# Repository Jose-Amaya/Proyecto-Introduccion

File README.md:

# Proyecto Introducción a la Ingeniería: Información sobre centrales de generación en Colombia

El proyecto consiste, en una estructura con un mapa de Colombia, el cuál tiene en cada punto donde hay una de las 47 centrales escogidas, un LED, el cuál estará encendido si la central en ese punto se encuentra en funcionamiento, y apagado si la central no está en funcionamiento, el color del LED depende del tipo de generación que se da en la central, y además hay un panel en donde se muestra la información de generación para cada central.

# Partes del proyecto

Para el desarrollo del proyecto:
1. Se editó el mapa para agregar la ubicacion de cada central, y las convenciones. [Abrir Carpeta](1.%20Diseño%20mapa/)
2. Se creó un programa en python que corre en una [Raspberri pi 3](https://www.raspberrypi.org/products/raspberry-pi-3-model-b/). [Abrir Carpeta](2.%20Programación/)
3. Se diseño una PCB, para controlar los 47 LEDs, con solo 16 pines ( o menos ) de la raspberry pi ( Por medio de una matriz de LEDS ) [Abrir Carpeta](3.%20PCB/)
4. Se diseño una página web para mostrar los datos de generación de las centrales en un panel. [Abrir Carpeta](4.%20Página%20web/)
5. Se diseño una estructura para contener todos los elementos.
6. Se consiguio información sobre las centrales de xm.com.co [Abrir Archivo Centrales.xlsx](6.%20Archivos/Centrales.xlsx)

Visitar cada carpeta para obtener mas información

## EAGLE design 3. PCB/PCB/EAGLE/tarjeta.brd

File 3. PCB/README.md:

# Archivos

## Orden de conexion

### tarjetaCentrales

En el archivo se encuentra el diseño de la PCB, y en cada puerto se indica la central a la que corresponde

## PCB

### tarjetaPCB

El diseño de la PCB

### tarjetaSchematic

El esquema del circuito

## EAGLE

Archivos del diseño y esquema para el programa [EAGLE](https://www.autodesk.com/education/free-software/eagle) de Autodesk

## Raspberry Pi

### pi3gpio

Numeración de los pines GPIO de la Raspberry Pi 3

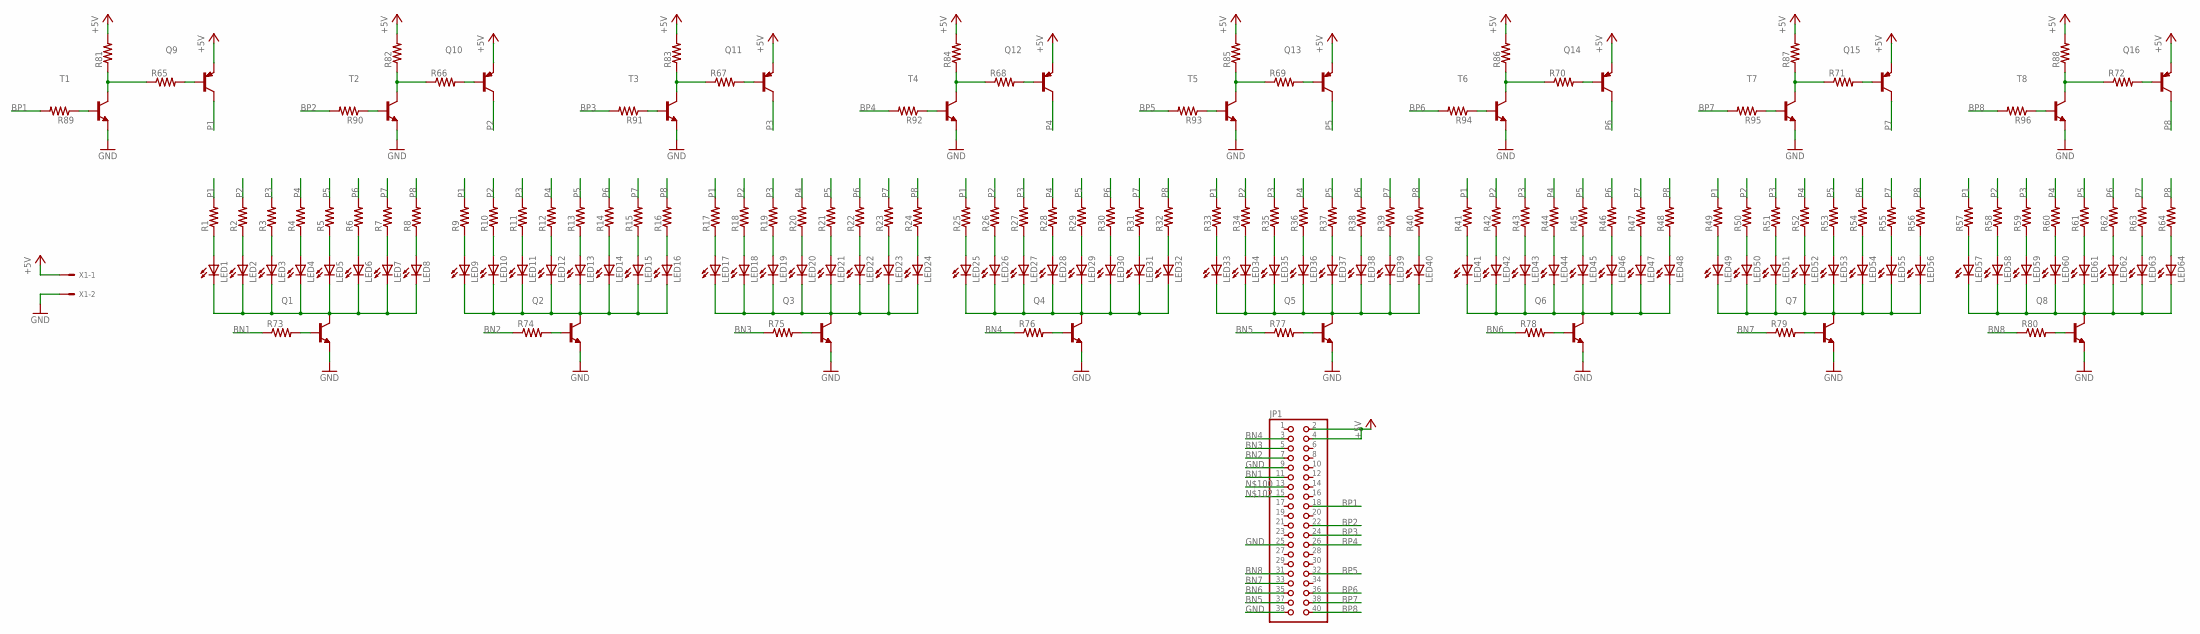
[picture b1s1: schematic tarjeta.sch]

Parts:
JP1: PINHD-2X20; 2X20
LED1, LED2, LED3, LED4, LED5, LED6, LED7, LED8, LED9, LED10, LED11, LED12, LED13, LED14, LED15, LED16, LED17, LED18, LED19, LED20, LED21, LED22, LED23, LED24, LED25, LED26, LED27, LED28, LED29, LED30, LED31, LED32, LED33, LED34, LED35, LED36, LED37, LED38, LED39, LED40, LED41, LED42, LED43, LED44, LED45, LED46, LED47, LED48, LED49, LED50, LED51, LED52, LED53, LED54, LED55, LED56, LED57, LED58, LED59, LED60, LED61, LED62, LED63, LED64: LED5MM
Q1, Q2, Q3, Q4, Q5, Q6, Q7, Q8: 2N2222TO92-CBE; TO92-CBE
Q9, Q10, Q11, Q12, Q13, Q14, Q15, Q16: 2N2907TO92-CBE; TO92-CBE
R1, R2, R3, R4, R5, R6, R7, R8, R9, R10, R11, R12, R13, R14, R15, R16, R17, R18, R19, R20, R21, R22, R23, R24, R25, R26, R27, R28, R29, R30, R31, R32, R33, R34, R35, R36, R37, R38, R39, R40, R41, R42, R43, R44, R45, R46, R47, R48, R49, R50, R51, R52, R53, R54, R55, R56, R57, R58, R59, R60, R61, R62, R63, R64, R65, R66, R67, R68, R69, R70, R71, R72, R73, R74, R75, R76, R77, R78, R79, R80, R81, R82, R83, R84, R85, R86, R87, R88, R89, R90, R91, R92, R93, R94, R95, R96: R-US_0204/7; 0204/7
T1, T2, T3, T4, T5, T6, T7, T8: 2N3904TO92-CBE; TO92-CBE
X1: KK-156-2

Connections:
+5V: JP1.2, JP1.4, Q9.E, Q10.E, Q11.E, Q12.E, Q13.E, Q14.E, Q15.E, Q16.E, R81.2, R82.2, R83.2, R84.2, R85.2, R86.2, R87.2, R88.2, X1.1
BN1: JP1.11, R73.1
BN2: JP1.7, R74.1
BN3: JP1.5, R75.1
BN4: JP1.3, R76.1
BN5: JP1.37, R77.1
BN6: JP1.35, R78.1
BN7: JP1.33, R79.1
BN8: JP1.31, R80.1
BP1: JP1.18, R89.2
BP2: JP1.22, R90.2
BP3: JP1.24, R91.2
BP4: JP1.26, R92.2
BP5: JP1.32, R93.2
BP6: JP1.36, R94.2
BP7: JP1.38, R95.2
BP8: JP1.40, R96.2
GND: JP1.9, JP1.25, JP1.39, Q1.E, Q2.E, Q3.E, Q4.E, Q5.E, Q6.E, Q7.E, Q8.E, T1.E, T2.E, T3.E, T4.E, T5.E, T6.E, T7.E, T8.E, X1.2
unnamed: LED1.K (C), LED2.K (C), LED3.K (C), LED4.K (C), LED5.K (C), LED6.K (C), LED7.K (C), LED8.K (C), Q1.C
unnamed: LED1.A, R1.1
unnamed: LED2.A, R2.1
unnamed: LED3.A, R3.1
unnamed: LED4.A, R4.1
unnamed: LED5.A, R5.1
unnamed: LED6.A, R6.1
unnamed: LED7.A, R7.1
unnamed: LED8.A, R8.1
unnamed: LED9.K (C), LED10.K (C), LED11.K (C), LED12.K (C), LED13.K (C), LED14.K (C), LED15.K (C), LED16.K (C), Q2.C
unnamed: LED9.A, R9.1
unnamed: LED10.A, R10.1
unnamed: LED11.A, R11.1
unnamed: LED12.A, R12.1
unnamed: LED13.A, R13.1
unnamed: LED14.A, R14.1
unnamed: LED15.A, R15.1
unnamed: LED16.A, R16.1
unnamed: LED17.K (C), LED18.K (C), LED19.K (C), LED20.K (C), LED21.K (C), LED22.K (C), LED23.K (C), LED24.K (C), Q3.C
unnamed: LED17.A, R17.1
unnamed: LED18.A, R18.1
unnamed: LED19.A, R19.1
unnamed: LED20.A, R20.1
unnamed: LED21.A, R21.1
unnamed: LED22.A, R22.1
unnamed: LED23.A, R23.1
unnamed: LED24.A, R24.1
unnamed: LED25.K (C), LED26.K (C), LED27.K (C), LED28.K (C), LED29.K (C), LED30.K (C), LED31.K (C), LED32.K (C), Q4.C
unnamed: LED25.A, R25.1
unnamed: LED26.A, R26.1
unnamed: LED27.A, R27.1
unnamed: LED28.A, R28.1
unnamed: LED29.A, R29.1
unnamed: LED30.A, R30.1
unnamed: LED31.A, R31.1
unnamed: LED32.A, R32.1
unnamed: LED33.K (C), LED34.K (C), LED35.K (C), LED36.K (C), LED37.K (C), LED38.K (C), LED39.K (C), LED40.K (C), Q5.C
unnamed: LED33.A, R33.1
unnamed: LED34.A, R34.1
unnamed: LED35.A, R35.1
unnamed: LED36.A, R36.1
unnamed: LED37.A, R37.1
unnamed: LED38.A, R38.1
unnamed: LED39.A, R39.1
unnamed: LED40.A, R40.1
unnamed: LED41.K (C), LED42.K (C), LED43.K (C), LED44.K (C), LED45.K (C), LED46.K (C), LED47.K (C), LED48.K (C), Q6.C
unnamed: LED41.A, R41.1
unnamed: LED42.A, R42.1
unnamed: LED43.A, R43.1
unnamed: LED44.A, R44.1
unnamed: LED45.A, R45.1
unnamed: LED46.A, R46.1
unnamed: LED47.A, R47.1
unnamed: LED48.A, R48.1
unnamed: LED49.K (C), LED50.K (C), LED51.K (C), LED52.K (C), LED53.K (C), LED54.K (C), LED55.K (C), LED56.K (C), Q7.C
unnamed: LED49.A, R49.1
unnamed: LED50.A, R50.1
unnamed: LED51.A, R51.1
unnamed: LED52.A, R52.1
unnamed: LED53.A, R53.1
unnamed: LED54.A, R54.1
unnamed: LED55.A, R55.1
unnamed: LED56.A, R56.1
unnamed: LED57.K (C), LED58.K (C), LED59.K (C), LED60.K (C), LED61.K (C), LED62.K (C), LED63.K (C), LED64.K (C), Q8.C
unnamed: LED57.A, R57.1
unnamed: LED58.A, R58.1
unnamed: LED59.A, R59.1
unnamed: LED60.A, R60.1
unnamed: LED61.A, R61.1
unnamed: LED62.A, R62.1
unnamed: LED63.A, R63.1
unnamed: LED64.A, R64.1
unnamed: Q9.B, R65.2
unnamed: R65.1, R81.1, T1.C
unnamed: R66.1, R82.1, T2.C
unnamed: Q10.B, R66.2
unnamed: R67.1, R83.1, T3.C
unnamed: Q11.B, R67.2
unnamed: R68.1, R84.1, T4.C
unnamed: Q12.B, R68.2
unnamed: R69.1, R85.1, T5.C
unnamed: Q13.B, R69.2
unnamed: R70.1, R86.1, T6.C
unnamed: Q14.B, R70.2
unnamed: R71.1, R87.1, T7.C
unnamed: Q15.B, R71.2
unnamed: R72.1, R88.1, T8.C
unnamed: Q16.B, R72.2
unnamed: Q8.B, R80.2
unnamed: Q7.B, R79.2
unnamed: Q6.B, R78.2
unnamed: Q5.B, R77.2
unnamed: Q4.B, R76.2
unnamed: Q3.B, R75.2
unnamed: Q2.B, R74.2
unnamed: Q1.B, R73.2
unnamed: R96.1, T8.B
unnamed: R95.1, T7.B
unnamed: R94.1, T6.B
unnamed: R93.1, T5.B
unnamed: R92.1, T4.B
unnamed: R91.1, T3.B
unnamed: R89.1, T1.B
unnamed: R90.1, T2.B
P1: Q9.C, R1.2, R9.2, R17.2, R25.2, R33.2, R41.2, R49.2, R57.2
P2: Q10.C, R2.2, R10.2, R18.2, R26.2, R34.2, R42.2, R50.2, R58.2
P3: Q11.C, R3.2, R11.2, R19.2, R27.2, R35.2, R43.2, R51.2, R59.2
P4: Q12.C, R4.2, R12.2, R20.2, R28.2, R36.2, R44.2, R52.2, R60.2
P5: Q13.C, R5.2, R13.2, R21.2, R29.2, R37.2, R45.2, R53.2, R61.2
P6: Q14.C, R6.2, R14.2, R22.2, R30.2, R38.2, R46.2, R54.2, R62.2
P7: Q15.C, R7.2, R15.2, R23.2, R31.2, R39.2, R47.2, R55.2, R63.2
P8: Q16.C, R8.2, R16.2, R24.2, R32.2, R40.2, R48.2, R56.2, R64.2

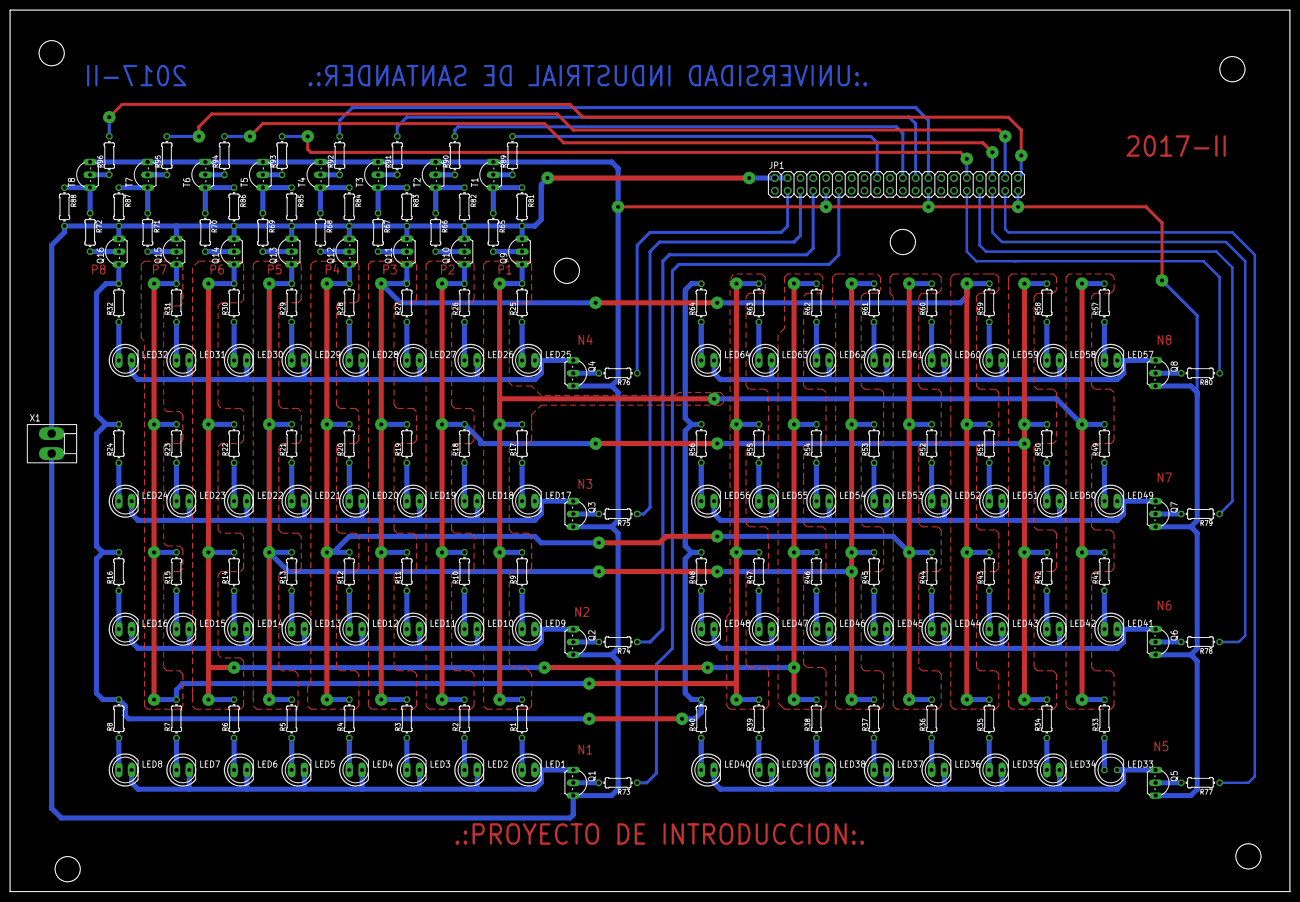
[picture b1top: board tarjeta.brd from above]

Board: 2 copper layers, 254.0 x 174.9 mm, 186 parts (0 on the bottom side), 130 nets.

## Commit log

2017-12-13 Programas
2017-12-13 Actualización
2017-12-13 Arreglo de errores
2017-12-13 Arreglo de errores y mejora de funciones
2017-12-13 Finalizado
2017-12-14 Se agrego codigo, con los pines para utilizar los programas con la PCB (Antes se usaban pines arbitrarios)
2017-12-14 Working
2017-12-14 Final
2017-12-14 Informacion
2017-12-14 Info
2017-12-16 finak
2017-12-17 finished
2018-02-03 Done
2018-02-17 Documentation
2018-02-18 Documentacion
2019-12-18 Upgrade
